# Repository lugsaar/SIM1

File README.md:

# SIM1

SIM1 oder Simulation One oder Simone ist der erste Step in dem Projekt, einen Roboter zu bauen, der ein interaktives Gespräch mit einem Moderator führt.

In der fertigen Ausbaustufe wird der Roboter auf Position des Moderatorengesichtes, erkannte Gestik, Keywords oder Sprache mit einer gesprochenen Antwort, Gestik und Mimik reagieren. Die Antwort kann durch AI generiert werden, damit erhält AI einen Avatar.

Simone ist die Basis dazu. Es wird eine Hardware/Software mit Sensoren und Aktuatoren entwickelt. Simone erfasst Vorgänge und gibt Antworten aus.

### Vorgänge sind
- Druck eines Tasters
- Gesten einer Hand
- Keywords
- Spracherkennung

### Antworten sind Einzel- und Sammelreaktionen

#### Einzelreaktionen 
- Einzelbewegungen von Arm und Kopf
- LED-Anzeigen der Augen
- Sprachantwort
- Mundanzeige Sprechen

#### Sammelreaktionen 
- Mundanzeigen wie Lachen, Trauer, Erstaunen, Grübeln
- Mundbewegungen Sprechen
- Aufmerksamkeit
- Jubelarme
- Palmface
- Nicken
- Kopfschütteln
- Schulterzucken

## HARDWARE

- Raspberry Pi 4B

### Sensoren um einen Vorgang zu erfassen
- Taster
- USB-Mikrofon
- USB-Kamera

### Aktuatoren um eine Reaktion darzustellen
- LED Auge links
- LED Auge rechts
- OLED Display als Mund
- Servo Arm rechts
- Servo Arm links
- Servo Pan, Kopf schwenken
- Servo Tilt, Kopf nicken
- USB-Soundkarte für Sprachausgabe

## SOFTWARE SIM1

Der erste Schritt ist der Theatermodus. Es werden vorgefertigte Antworten aus Gestik und Text sukzessiv wiedergegeben.

###  Version 0.1 Theatermodus
- Auslöser der ersten Antwort ist ein Tastendruck
- Auslöser der Folgeantworten sind Tastendruck oder abgelaufene Zeit 
- Nur Einzelreaktionen
- Mundbewegung als simple Balkengrafik
- Inhalte einer Antwort sind mehrere Reaktionen, die gleichzeitig oder sukzessiv abgespielt werden 
- Die in den Antworten auszugebende Sprache liegt als Textfile vor
- Ablage-Format der Antworten: Json

## HARDWARE Sim1 Version 0.1

- Aufbau auf Entwicklungsbord
- Servo Arm links
- Servo Head Pan (Kopf drehen)
- OLED Display 128x64, i2c-Anschluß
- USB-Soundkarte für Sprachausgabe

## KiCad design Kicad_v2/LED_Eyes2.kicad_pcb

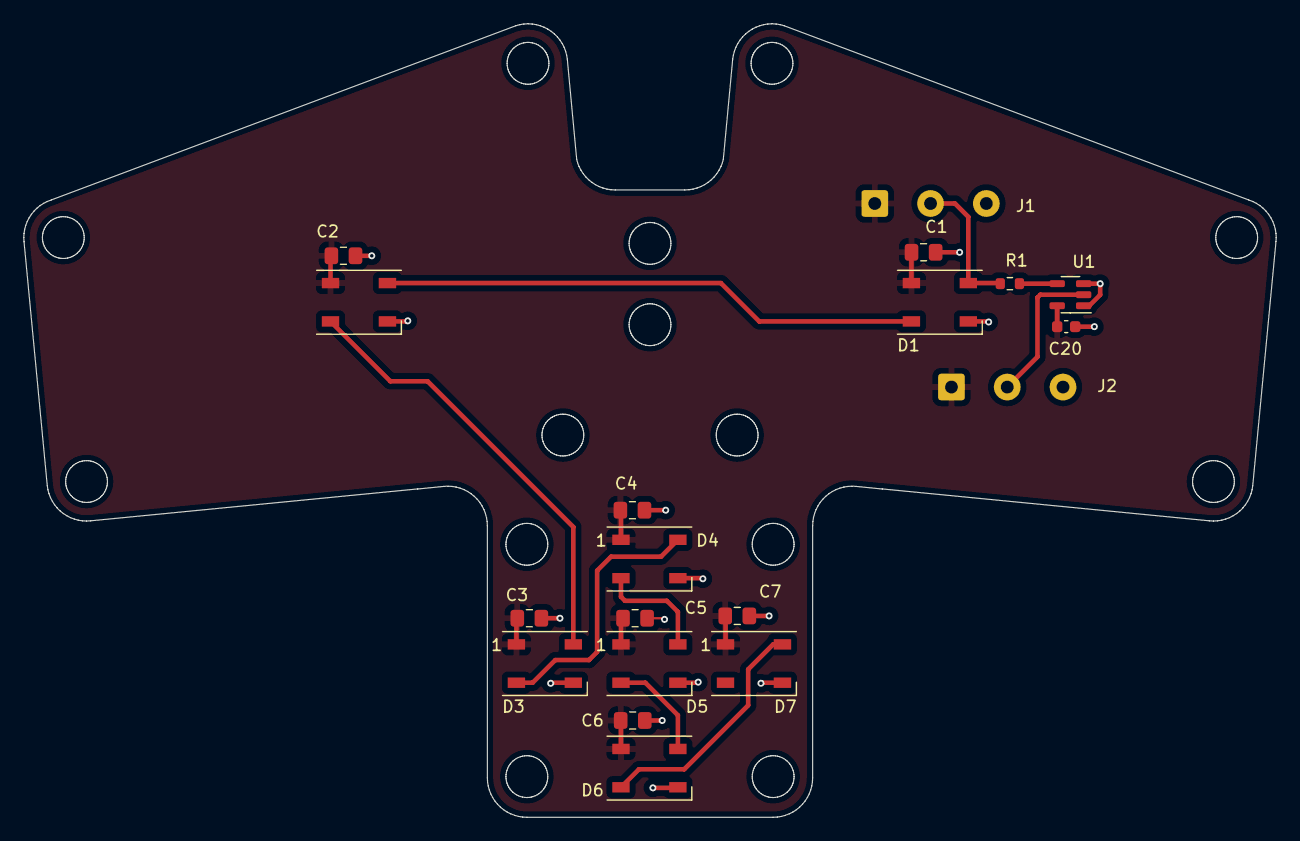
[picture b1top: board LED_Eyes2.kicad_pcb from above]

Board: 2 copper layers, 107.8 x 68.3 mm, 19 parts (0 on the bottom side), 11 nets.

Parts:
C1, C2, C3, C4, C5, C6, C7: 100n; C_0805_2012Metric_Pad1.18x1.45mm_HandSolder
C20: 100n; C_0603_1608Metric
D1, D2, D3, D4, D5, D6, D7: WS2812B; LED_WS2812B_PLCC4_5.0x5.0mm_P3.2mm
J1, J2: Conn_01x03; SolderWire-0.5sqmm_1x03_P4.8mm_D0.9mm_OD2.3mm
R1: 470R; R_0603_1608Metric
U1: 74LVC1G17; SOT-23-5

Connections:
+5V: C1.1, C2.1, C3.1, C4.1, C5.1, C6.1, C7.1, C20.1, D1.1 (VDD), D2.1 (VDD), D3.1 (VDD), D4.1 (VDD), D5.1 (VDD), D6.1 (VDD), D7.1 (VDD), J1.1, J2.1, U1.5 (VCC)
GND: C1.2, C2.2, C3.2, C4.2, C5.2, C6.2, C7.2, C20.2, D1.3 (VSS), D2.3 (VSS), D3.3 (VSS), D4.3 (VSS), D5.3 (VSS), D6.3 (VSS), D7.3 (VSS), J1.3, J2.3, U1.1, U1.3 (GND)
unnamed: D1.4 (DIN), J1.2, R1.1
unnamed: D1.2 (DOUT), D2.4 (DIN)
unnamed: D2.2 (DOUT), D3.4 (DIN)
unnamed: D3.2 (DOUT), D4.4 (DIN)
unnamed: D4.2 (DOUT), D5.4 (DIN)
unnamed: D5.2 (DOUT), D6.4 (DIN)
unnamed: D6.2 (DOUT), D7.4 (DIN)
unnamed: J2.2, U1.2
unnamed: R1.2, U1.4

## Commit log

2023-07-28 Projektbeschreibung
2023-07-31 Development Hardware
2023-08-01 Definition Json File
2023-08-02 Button
2023-08-03 mouthspeak SW Definition
2023-08-03 Software Ideas
2023-08-04 espeak2 works with json
2023-08-29 simone wakes up
2023-10-07 LED_on_PCB Eyes
2023-10-10 PCB_Layout sketched
2023-10-13 PCB routed
2023-10-15 PCB Vorderseite 5V, Rückseite GND
2023-10-18 PCB Version 2
2023-10-21 PCB CU-lines improved
2023-10-21 w/w w/o Pegelshifter
2023-10-23 Leiterbahnenbreite
2023-10-23 Gerber Files
